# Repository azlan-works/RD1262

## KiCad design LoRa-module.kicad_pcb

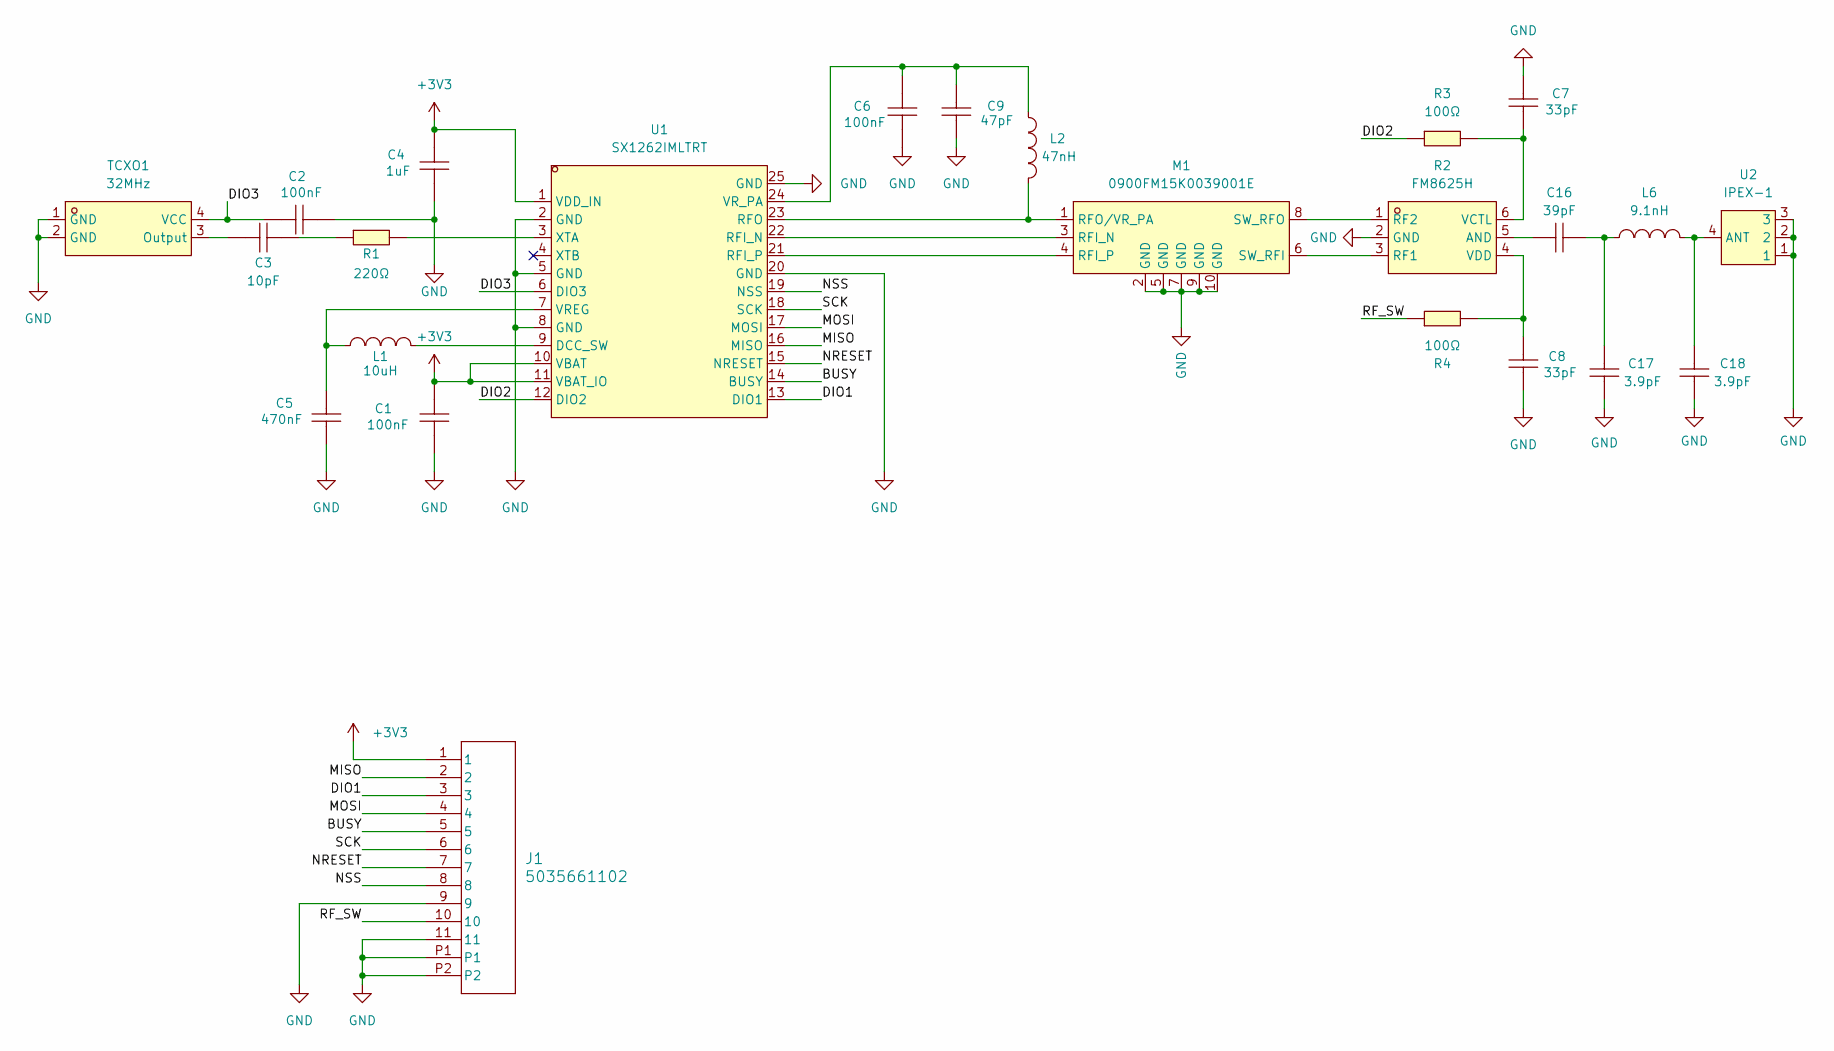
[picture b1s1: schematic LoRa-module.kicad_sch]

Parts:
C1, C2, C6: 100nF; C0402; LCSC Part C307331
C3: 10pF; C0402; LCSC Part C32949
C4: 1uF; C0402; LCSC Part C52923
C5: 470nF; C0402; LCSC Part C47339
C7, C8: 33pF; C0402; LCSC Part C1562
C9: 47pF; C0402; LCSC Part C1567
C16: 39pF; C0402; LCSC Part C3847304
C17, C18: 3.9pF; C0402; LCSC Part C88893
J1: 5035661102; CON_5035661102_MOL; LCSC Part C3036270
L1: 10uH; L0805; LCSC Part C162582
L2: 47nH; L0402; LCSC Part C22334
L6: 9.1nH; L0402; LCSC Part C113122
M1: 0900FM15K0039001E; FILTER-SMD_10P-L2.0-W1.3-BL; LCSC Part C7434807
R1: 220Ω; R0402; LCSC Part C25091
R2: FM8625H; DFN-6_L1.1-W0.7-P0.40-BL; LCSC Part C2857391
R3, R4: 100Ω; R0402; LCSC Part C25076
TCXO1: 32MHz; OSC-SMD_4P-L2.0-W1.6-BL_1XXD; LCSC Part C253694
U1: SX1262IMLTRT; QFN-24_L4.0-W4.0-P0.50-BL-EP2.6; LCSC Part C191341
U2: IPEX-1; IPEX-SMD_4P-L2.6-W2.6-LS3.0; LCSC Part C2987682

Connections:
+3V3: C1.2, C4.2, J1.1, U1.1 (VDD_IN), U1.10 (VBAT), U1.11 (VBAT_IO)
/BUSY: J1.5, U1.14 (BUSY)
/DIO1: J1.3, U1.13 (DIO1)
/DIO2: R3.1, U1.12 (DIO2)
/DIO3: C2.2, TCXO1.4 (VCC), U1.6 (DIO3)
/MISO: J1.2, U1.16 (MISO)
/MOSI: J1.4, U1.17 (MOSI)
/NRESET: J1.7, U1.15 (NRESET)
/NSS: J1.8, U1.19 (NSS)
/RF_SW: J1.10, R4.1
/SCK: J1.6, U1.18 (SCK)
GND: C1.1, C2.1, C4.1, C5.1, C6.1, C7.2, C8.1, C9.1, C17.1, C18.1, J1.9, J1.11, J1.P1, J1.P2, M1.2 (GND), M1.5 (GND), M1.7 (GND), M1.9 (GND), M1.10 (GND), R2.2 (GND), TCXO1.1 (GND), TCXO1.2 (GND), U1.2 (GND), U1.5 (GND), U1.8 (GND), U1.20 (GND), U1.25 (GND), U2.1, U2.2, U2.3
unnamed: C3.2, R1.1
unnamed: C16.2, C17.2, L6.2
unnamed: M1.3 (RFI_N), U1.22 (RFI_N)
unnamed: M1.4 (RFI_P), U1.21 (RFI_P)
unnamed: L2.1, M1.1 (RFO/VR_PA), U1.23 (RFO)
unnamed: M1.6 (SW_RFI), R2.3 (RF1)
unnamed: M1.8 (SW_RFO), R2.1 (RF2)
unnamed: C16.1, R2.5 (AND)
unnamed: C7.1, R2.6 (VCTL), R3.2
unnamed: C8.2, R2.4 (VDD), R4.2
unnamed: C3.1, TCXO1.3 (Output)
unnamed: L1.1, U1.9 (DCC_SW)
unnamed: C5.2, L1.2, U1.7 (VREG)
unnamed: C6.2, C9.2, L2.2, U1.24 (VR_PA)
unnamed: R1.2, U1.3 (XTA)
unnamed: C18.2, L6.1, U2.4 (ANT)

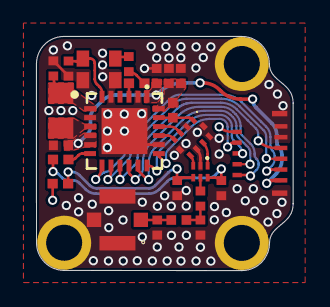
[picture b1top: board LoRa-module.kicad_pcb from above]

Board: 6 copper layers, 14.3 x 13.0 mm, 24 parts (0 on the bottom side), 28 nets.

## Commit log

2026-06-24 Updated FPC pinout
